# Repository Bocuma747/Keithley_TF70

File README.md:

# Keithley_TF70
 
A drop-in replacement PCB for the Keithley TF-70 resistor network found in Keithley 172A and 173A multimeters. This is R615 in Rev B instruments, as found in the A/D converter section of the service manual.

Bill of materials is located in BOM.csv. For maximum performance, I recommend 0.1% tolerance resistors with the lowest temperature coefficient available.
The header pins are generic right-angle header pins with 0.1" (2.54mm) pitch, the same as on breadboards.

The PCB can be ordered from any of the usual PCB fabs by uploading Gerber.zip. No special requirements should be necessary.

Original resistor network, exposed and labeled to show the inner resistors and pin numbers:

Schematic:

Replacement:

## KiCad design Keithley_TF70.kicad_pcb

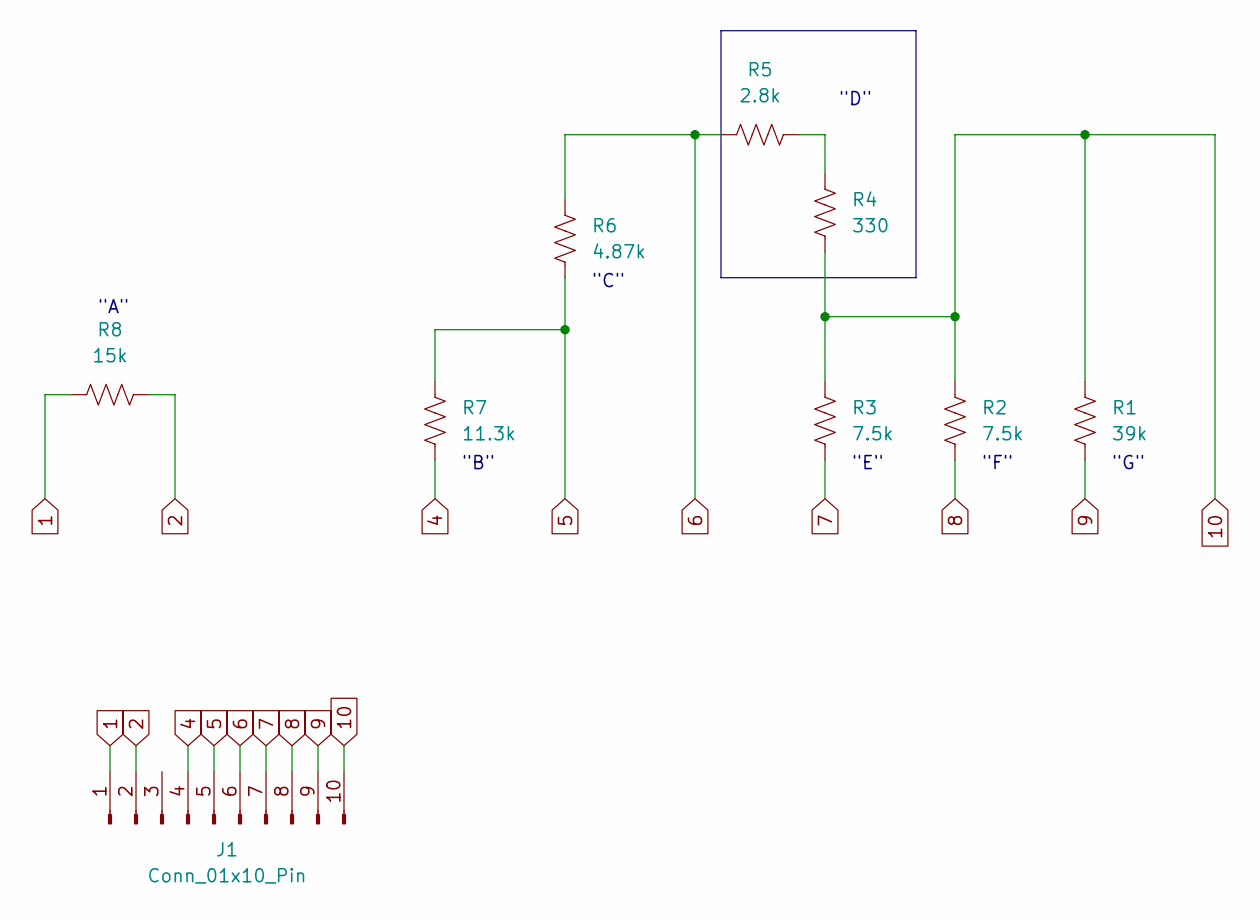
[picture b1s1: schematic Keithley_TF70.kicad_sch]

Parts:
J1: Conn_01x10_Pin; PinHeader_1x10_P2.54mm_Vertical
R1: 39k; R_0805_2012Metric_Pad1.20x1.40mm_HandSolder
R2, R3: 7.5k; R_0805_2012Metric_Pad1.20x1.40mm_HandSolder
R4: 330; R_0805_2012Metric_Pad1.20x1.40mm_HandSolder
R5: 2.8k; R_0805_2012Metric_Pad1.20x1.40mm_HandSolder
R6: 4.87k; R_0805_2012Metric_Pad1.20x1.40mm_HandSolder
R7: 11.3k; R_0805_2012Metric_Pad1.20x1.40mm_HandSolder
R8: 15k; R_0805_2012Metric_Pad1.20x1.40mm_HandSolder

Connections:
1: J1.1, R8.1
2: J1.2, R8.2
4: J1.4, R7.1
5: J1.5, R6.1, R7.2
6: J1.6, R5.2, R6.2
7: J1.7, R3.2
8: J1.8, R2.2
9: J1.9, R1.2
10: J1.10, R1.1, R2.1, R3.1, R4.2
unnamed: R4.1, R5.1

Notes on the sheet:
"F"
"C"
"G"
"D"
"E"
"A"
"B"

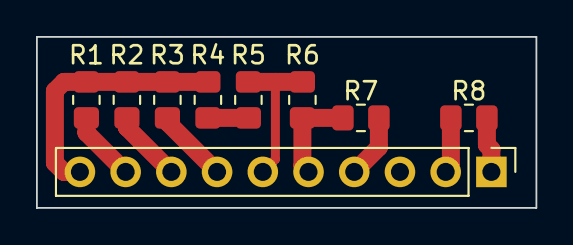
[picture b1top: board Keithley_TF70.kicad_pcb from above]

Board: 2 copper layers, 27.8 x 9.5 mm, 9 parts (0 on the bottom side), 10 nets.

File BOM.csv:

Date:,10/1/2023 1:47:02 PM,,,,,,
Tool:,Eeschema 7.0.5,,,,,,
Generator:,C:\Program Files\KiCad\7.0\bin\scripting\plugins/bom_csv_grouped_by_value_with_fp.py,,,,,,
Component Count:,9,,,,,,
Ref,Qnty,Value,Cmp name,Footprint,Description,Vendor,DNP
J1,1,Conn_01x10_Pin,Conn_01x10_Pin,Connector_PinHeader_2.54mm:PinHeader_1x10_P2.54mm_Vertical,"Generic connector, single row, 01x10, script generated",,
R1,1,39k,R_US,Resistor_SMD:R_0805_2012Metric_Pad1.20x1.40mm_HandSolder,"Resistor, US symbol",,
"R2, R3",2,7.5k,R_US,Resistor_SMD:R_0805_2012Metric_Pad1.20x1.40mm_HandSolder,"Resistor, US symbol",,
R4,1,330,R_US,Resistor_SMD:R_0805_2012Metric_Pad1.20x1.40mm_HandSolder,"Resistor, US symbol",,
R5,1,2.8k,R_US,Resistor_SMD:R_0805_2012Metric_Pad1.20x1.40mm_HandSolder,"Resistor, US symbol",,
R6,1,4.87k,R_US,Resistor_SMD:R_0805_2012Metric_Pad1.20x1.40mm_HandSolder,"Resistor, US symbol",,
R7,1,11.3k,R_US,Resistor_SMD:R_0805_2012Metric_Pad1.20x1.40mm_HandSolder,"Resistor, US symbol",,
R8,1,15k,R_US,Resistor_SMD:R_0805_2012Metric_Pad1.20x1.40mm_HandSolder,"Resistor, US symbol",,

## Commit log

2023-10-11 Added attribution text and gerber files
2023-10-11 Uploaded images
2023-10-11 Added BOM
2023-10-11 Added images
